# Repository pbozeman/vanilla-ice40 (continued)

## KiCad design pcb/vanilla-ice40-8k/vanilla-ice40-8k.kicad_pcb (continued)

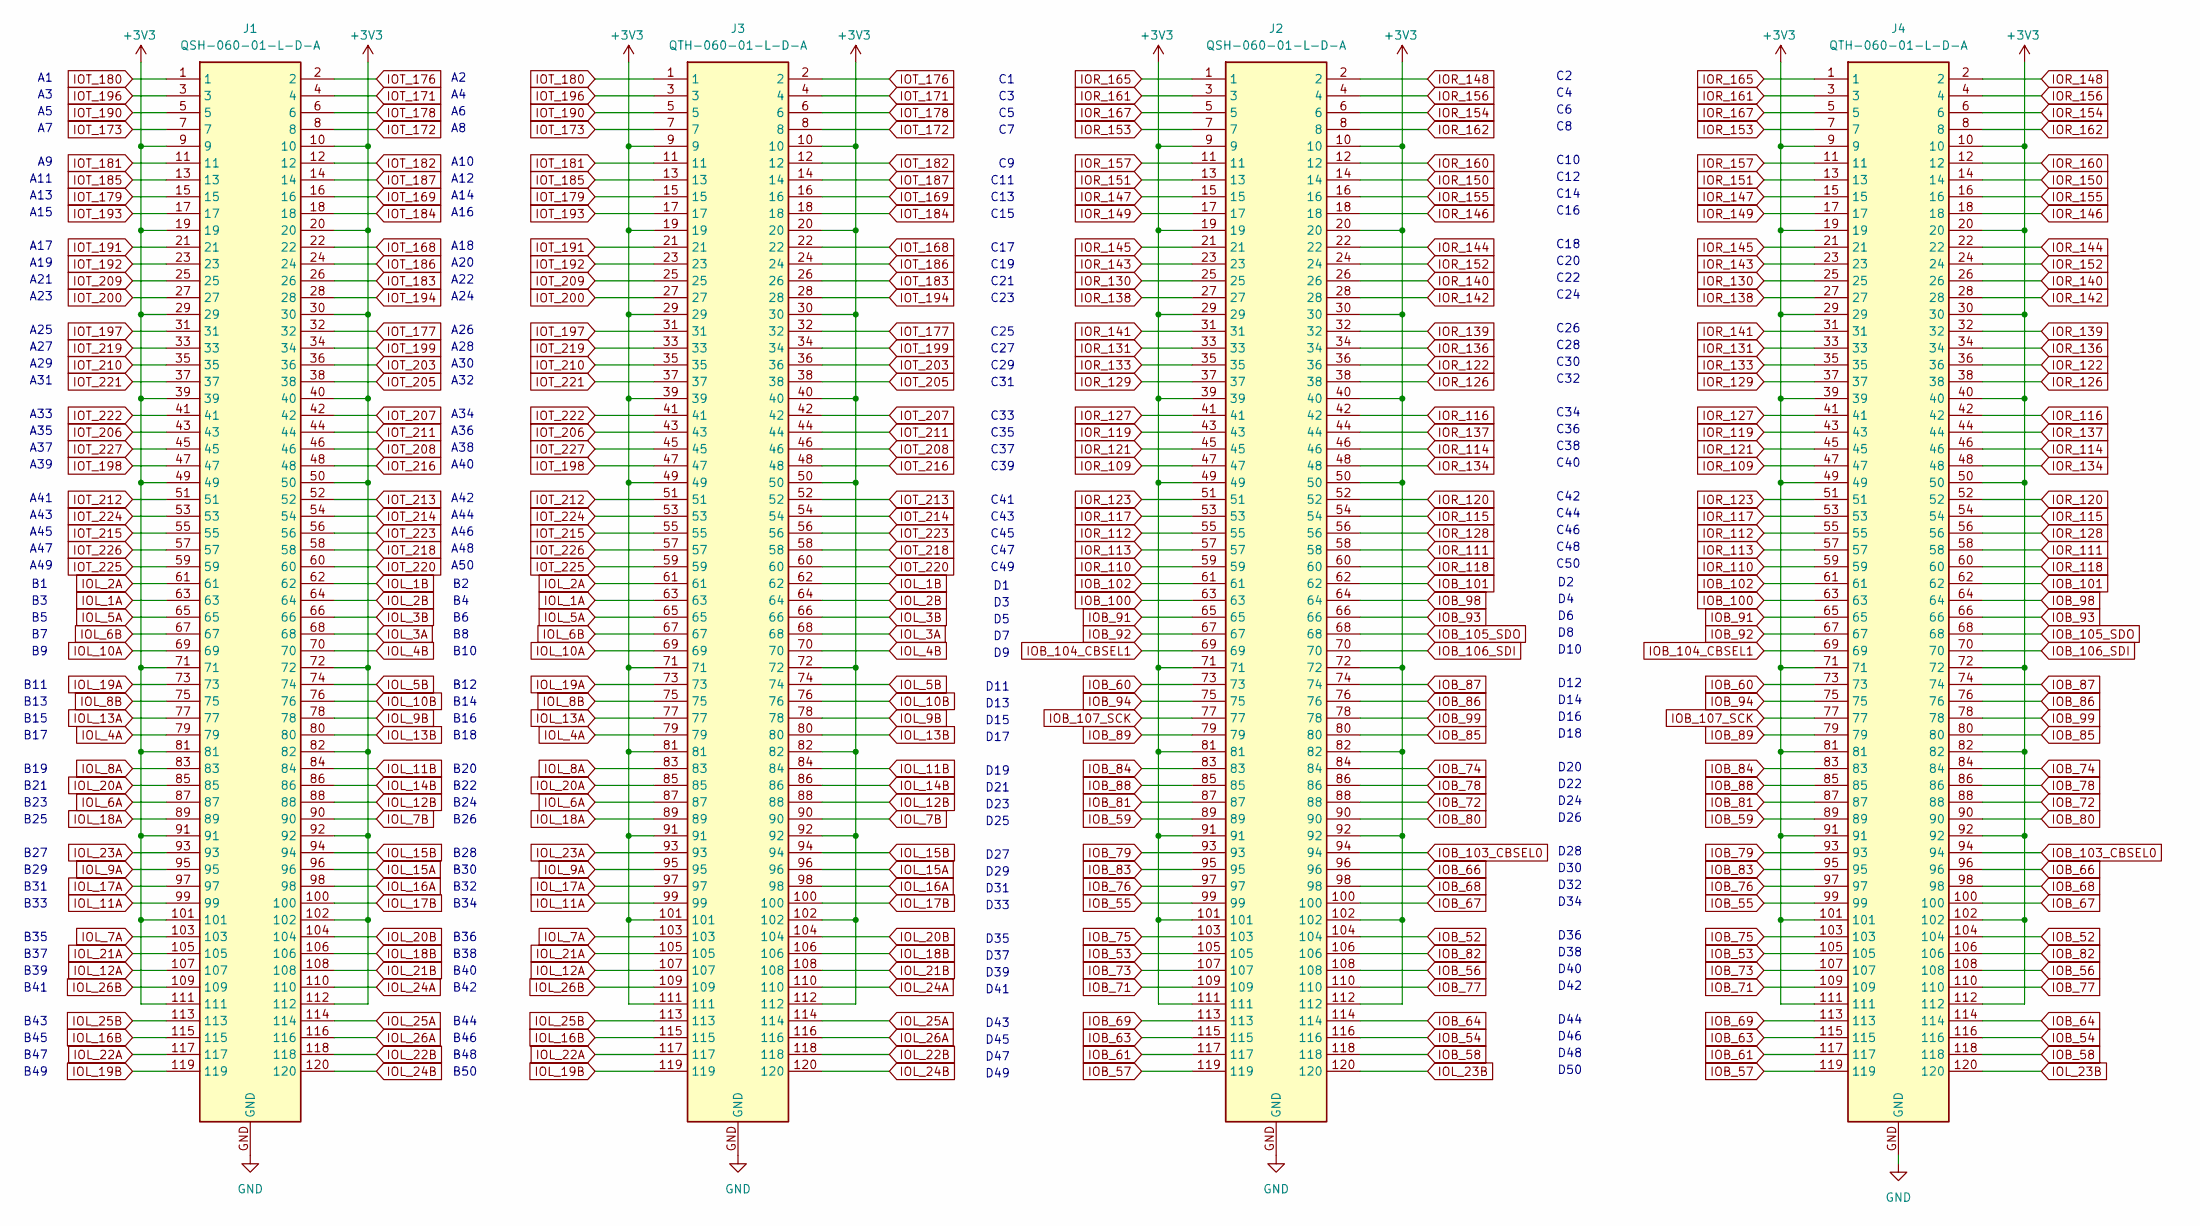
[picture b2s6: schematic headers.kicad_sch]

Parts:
J1, J2: QSH-060-01-L-D-A; SAMTEC_QSH-060-01-X-D-A
J3, J4: QTH-060-01-L-D-A; SAMTEC_QTH-060-01-X-D-A

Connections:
+3V3: J1.9, J1.10, J1.19, J1.20, J1.29, J1.30, J1.39, J1.40, J1.49, J1.50, J1.71, J1.72, J1.81, J1.82, J1.91, J1.92, J1.101, J1.102, J1.111, J1.112, J2.9, J2.10, J2.19, J2.20, J2.29, J2.30, J2.39, J2.40, J2.49, J2.50, J2.71, J2.72, J2.81, J2.82, J2.91, J2.92, J2.101, J2.102, J2.111, J2.112, J3.9, J3.10, J3.19, J3.20, J3.29, J3.30, J3.39, J3.40, J3.49, J3.50, J3.71, J3.72, J3.81, J3.82, J3.91, J3.92, J3.101, J3.102, J3.111, J3.112, J4.9, J4.10, J4.19, J4.20, J4.29, J4.30, J4.39, J4.40, J4.49, J4.50, J4.71, J4.72, J4.81, J4.82, J4.91, J4.92, J4.101, J4.102, J4.111, J4.112; also elsewhere on the board
GND: J1.GND, J2.GND, J3.GND, J4.GND; also elsewhere on the board
IOB_52: J2.104, J4.104; also elsewhere on the board
IOB_53: J2.105, J4.105; also elsewhere on the board
IOB_54: J2.116, J4.116; also elsewhere on the board
IOB_55: J2.99, J4.99; also elsewhere on the board
IOB_56: J2.108, J4.108; also elsewhere on the board
IOB_57: J2.119, J4.119; also elsewhere on the board
IOB_58: J2.118, J4.118; also elsewhere on the board
IOB_59: J2.89, J4.89; also elsewhere on the board
IOB_60: J2.73, J4.73; also elsewhere on the board
IOB_61: J2.117, J4.117; also elsewhere on the board
IOB_63: J2.115, J4.115; also elsewhere on the board
IOB_64: J2.114, J4.114; also elsewhere on the board
IOB_66: J2.96, J4.96; also elsewhere on the board
IOB_67: J2.100, J4.100; also elsewhere on the board
IOB_68: J2.98, J4.98; also elsewhere on the board
IOB_69: J2.113, J4.113; also elsewhere on the board
IOB_71: J2.109, J4.109; also elsewhere on the board
IOB_72: J2.88, J4.88; also elsewhere on the board
IOB_73: J2.107, J4.107; also elsewhere on the board
IOB_74: J2.84, J4.84; also elsewhere on the board
IOB_75: J2.103, J4.103; also elsewhere on the board
IOB_76: J2.97, J4.97; also elsewhere on the board
IOB_77: J2.110, J4.110; also elsewhere on the board
IOB_78: J2.86, J4.86; also elsewhere on the board
IOB_79: J2.93, J4.93; also elsewhere on the board
IOB_80: J2.90, J4.90; also elsewhere on the board
IOB_81: J2.87, J4.87; also elsewhere on the board
IOB_82: J2.106, J4.106; also elsewhere on the board
IOB_83: J2.95, J4.95; also elsewhere on the board
IOB_84: J2.83, J4.83; also elsewhere on the board
IOB_85: J2.80, J4.80; also elsewhere on the board
IOB_86: J2.76, J4.76; also elsewhere on the board
IOB_87: J2.74, J4.74; also elsewhere on the board
IOB_88: J2.85, J4.85; also elsewhere on the board
IOB_89: J2.79, J4.79; also elsewhere on the board
IOB_91: J2.65, J4.65; also elsewhere on the board
IOB_92: J2.67, J4.67; also elsewhere on the board
IOB_93: J2.66, J4.66; also elsewhere on the board
IOB_94: J2.75, J4.75; also elsewhere on the board
IOB_98: J2.64, J4.64; also elsewhere on the board
IOB_99: J2.78, J4.78; also elsewhere on the board
IOB_100: J2.63, J4.63; also elsewhere on the board
IOB_101: J2.62, J4.62; also elsewhere on the board
IOB_102: J2.61, J4.61; also elsewhere on the board
IOB_103_CBSEL0: J2.94, J4.94; also elsewhere on the board
IOB_104_CBSEL1: J2.69, J4.69; also elsewhere on the board
IOB_105_SDO: J2.68, J4.68; also elsewhere on the board
IOB_106_SDI: J2.70, J4.70; also elsewhere on the board
IOB_107_SCK: J2.77, J4.77; also elsewhere on the board
IOL_1A: J1.63, J3.63; also elsewhere on the board
IOL_1B: J1.62, J3.62; also elsewhere on the board
IOL_2A: J1.61, J3.61; also elsewhere on the board
IOL_2B: J1.64, J3.64; also elsewhere on the board
IOL_3A: J1.68, J3.68; also elsewhere on the board
IOL_3B: J1.66, J3.66; also elsewhere on the board
IOL_4A: J1.79, J3.79; also elsewhere on the board
IOL_4B: J1.70, J3.70; also elsewhere on the board
IOL_5A: J1.65, J3.65; also elsewhere on the board
IOL_5B: J1.74, J3.74; also elsewhere on the board
IOL_6A: J1.87, J3.87; also elsewhere on the board
IOL_6B: J1.67, J3.67; also elsewhere on the board
IOL_7A: J1.103, J3.103; also elsewhere on the board
IOL_7B: J1.90, J3.90; also elsewhere on the board
IOL_8A: J1.83, J3.83; also elsewhere on the board
IOL_8B: J1.75, J3.75; also elsewhere on the board
IOL_9A: J1.95, J3.95; also elsewhere on the board
IOL_9B: J1.78, J3.78; also elsewhere on the board
IOL_10A: J1.69, J3.69; also elsewhere on the board
IOL_10B: J1.76, J3.76; also elsewhere on the board
IOL_11A: J1.99, J3.99; also elsewhere on the board
IOL_11B: J1.84, J3.84; also elsewhere on the board
IOL_12A: J1.107, J3.107; also elsewhere on the board
IOL_12B: J1.88, J3.88; also elsewhere on the board
IOL_13A: J1.77, J3.77; also elsewhere on the board
IOL_13B: J1.80, J3.80; also elsewhere on the board
IOL_14B: J1.86, J3.86; also elsewhere on the board
IOL_15A: J1.96, J3.96; also elsewhere on the board
IOL_15B: J1.94, J3.94; also elsewhere on the board
IOL_16A: J1.98, J3.98; also elsewhere on the board
IOL_16B: J1.115, J3.115; also elsewhere on the board
IOL_17A: J1.97, J3.97; also elsewhere on the board
IOL_17B: J1.100, J3.100; also elsewhere on the board
IOL_18A: J1.89, J3.89; also elsewhere on the board
IOL_18B: J1.106, J3.106; also elsewhere on the board
IOL_19A: J1.73, J3.73; also elsewhere on the board
IOL_19B: J1.119, J3.119; also elsewhere on the board
IOL_20A: J1.85, J3.85; also elsewhere on the board
IOL_20B: J1.104, J3.104; also elsewhere on the board
IOL_21A: J1.105, J3.105; also elsewhere on the board
IOL_21B: J1.108, J3.108; also elsewhere on the board
IOL_22A: J1.117, J3.117; also elsewhere on the board
IOL_22B: J1.118, J3.118; also elsewhere on the board
IOL_23A: J1.93, J3.93; also elsewhere on the board
IOL_23B: J2.120, J4.120; also elsewhere on the board
IOL_24A: J1.110, J3.110; also elsewhere on the board
IOL_24B: J1.120, J3.120; also elsewhere on the board
IOL_25A: J1.114, J3.114; also elsewhere on the board
IOL_25B: J1.113, J3.113; also elsewhere on the board
IOL_26A: J1.116, J3.116; also elsewhere on the board
IOL_26B: J1.109, J3.109; also elsewhere on the board
IOR_109: J2.47, J4.47; also elsewhere on the board
IOR_110: J2.59, J4.59; also elsewhere on the board
IOR_111: J2.58, J4.58; also elsewhere on the board
IOR_112: J2.55, J4.55; also elsewhere on the board
IOR_113: J2.57, J4.57; also elsewhere on the board
IOR_114: J2.46, J4.46; also elsewhere on the board
IOR_115: J2.54, J4.54; also elsewhere on the board
IOR_116: J2.42, J4.42; also elsewhere on the board
IOR_117: J2.53, J4.53; also elsewhere on the board
IOR_118: J2.60, J4.60; also elsewhere on the board
IOR_119: J2.43, J4.43; also elsewhere on the board
IOR_120: J2.52, J4.52; also elsewhere on the board
IOR_121: J2.45, J4.45; also elsewhere on the board
IOR_122: J2.36, J4.36; also elsewhere on the board
IOR_123: J2.51, J4.51; also elsewhere on the board
IOR_126: J2.38, J4.38; also elsewhere on the board
IOR_127: J2.41, J4.41; also elsewhere on the board
IOR_128: J2.56, J4.56; also elsewhere on the board
IOR_129: J2.37, J4.37; also elsewhere on the board
IOR_130: J2.25, J4.25; also elsewhere on the board
IOR_131: J2.33, J4.33; also elsewhere on the board
IOR_133: J2.35, J4.35; also elsewhere on the board
IOR_134: J2.48, J4.48; also elsewhere on the board
IOR_136: J2.34, J4.34; also elsewhere on the board
IOR_137: J2.44, J4.44; also elsewhere on the board
IOR_138: J2.27, J4.27; also elsewhere on the board
IOR_139: J2.32, J4.32; also elsewhere on the board
IOR_140: J2.26, J4.26; also elsewhere on the board
IOR_141: J2.31, J4.31; also elsewhere on the board
IOR_142: J2.28, J4.28; also elsewhere on the board
IOR_143: J2.23, J4.23; also elsewhere on the board
IOR_144: J2.22, J4.22; also elsewhere on the board
IOR_145: J2.21, J4.21; also elsewhere on the board
IOR_146: J2.18, J4.18; also elsewhere on the board
IOR_147: J2.15, J4.15; also elsewhere on the board
IOR_148: J2.2, J4.2; also elsewhere on the board
IOR_149: J2.17, J4.17; also elsewhere on the board
IOR_150: J2.14, J4.14; also elsewhere on the board
IOR_151: J2.13, J4.13; also elsewhere on the board
IOR_152: J2.24, J4.24; also elsewhere on the board
IOR_153: J2.7, J4.7; also elsewhere on the board
IOR_154: J2.6, J4.6; also elsewhere on the board
IOR_155: J2.16, J4.16; also elsewhere on the board
IOR_156: J2.4, J4.4; also elsewhere on the board
IOR_157: J2.11, J4.11; also elsewhere on the board
IOR_160: J2.12, J4.12; also elsewhere on the board
IOR_161: J2.3, J4.3; also elsewhere on the board
IOR_162: J2.8, J4.8; also elsewhere on the board
IOR_165: J2.1, J4.1; also elsewhere on the board
IOR_167: J2.5, J4.5; also elsewhere on the board
IOT_168: J1.22, J3.22; also elsewhere on the board
IOT_169: J1.16, J3.16; also elsewhere on the board
IOT_171: J1.4, J3.4; also elsewhere on the board
IOT_172: J1.8, J3.8; also elsewhere on the board
IOT_173: J1.7, J3.7; also elsewhere on the board
IOT_176: J1.2, J3.2; also elsewhere on the board
IOT_177: J1.32, J3.32; also elsewhere on the board
IOT_178: J1.6, J3.6; also elsewhere on the board
IOT_179: J1.15, J3.15; also elsewhere on the board
IOT_180: J1.1, J3.1; also elsewhere on the board
IOT_181: J1.11, J3.11; also elsewhere on the board
IOT_182: J1.12, J3.12; also elsewhere on the board
IOT_183: J1.26, J3.26; also elsewhere on the board
IOT_184: J1.18, J3.18; also elsewhere on the board
IOT_185: J1.13, J3.13; also elsewhere on the board
IOT_186: J1.24, J3.24; also elsewhere on the board
IOT_187: J1.14, J3.14; also elsewhere on the board
IOT_190: J1.5, J3.5; also elsewhere on the board
IOT_191: J1.21, J3.21; also elsewhere on the board
IOT_192: J1.23, J3.23; also elsewhere on the board
IOT_193: J1.17, J3.17; also elsewhere on the board
IOT_194: J1.28, J3.28; also elsewhere on the board
IOT_196: J1.3, J3.3; also elsewhere on the board
IOT_197: J1.31, J3.31; also elsewhere on the board
IOT_198: J1.47, J3.47; also elsewhere on the board
IOT_199: J1.34, J3.34; also elsewhere on the board
IOT_200: J1.27, J3.27; also elsewhere on the board
IOT_203: J1.36, J3.36; also elsewhere on the board
IOT_205: J1.38, J3.38; also elsewhere on the board
IOT_206: J1.43, J3.43; also elsewhere on the board
IOT_207: J1.42, J3.42; also elsewhere on the board
IOT_208: J1.46, J3.46; also elsewhere on the board
IOT_209: J1.25, J3.25; also elsewhere on the board
IOT_210: J1.35, J3.35; also elsewhere on the board
IOT_211: J1.44, J3.44; also elsewhere on the board
IOT_212: J1.51, J3.51; also elsewhere on the board
IOT_213: J1.52, J3.52; also elsewhere on the board
IOT_214: J1.54, J3.54; also elsewhere on the board
IOT_215: J1.55, J3.55; also elsewhere on the board
IOT_216: J1.48, J3.48; also elsewhere on the board
IOT_218: J1.58, J3.58; also elsewhere on the board
IOT_219: J1.33, J3.33; also elsewhere on the board
IOT_220: J1.60, J3.60; also elsewhere on the board
IOT_221: J1.37, J3.37; also elsewhere on the board
IOT_222: J1.41, J3.41; also elsewhere on the board
IOT_223: J1.56, J3.56; also elsewhere on the board
IOT_224: J1.53, J3.53; also elsewhere on the board
IOT_225: J1.59, J3.59; also elsewhere on the board
IOT_226: J1.57, J3.57; also elsewhere on the board
IOT_227: J1.45, J3.45; also elsewhere on the board

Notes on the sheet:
C41
C23
C16
B42
B10
C43
B33
B31
B15
C30
D17
A38
D41
B24
B25
C50
D42
C14
C33
B13
D19
C18
A22
D18
A37
A28
A17
A33
D25
B21
D15
B23
B22
D21
A35
A42
D12
C48
C25
D31

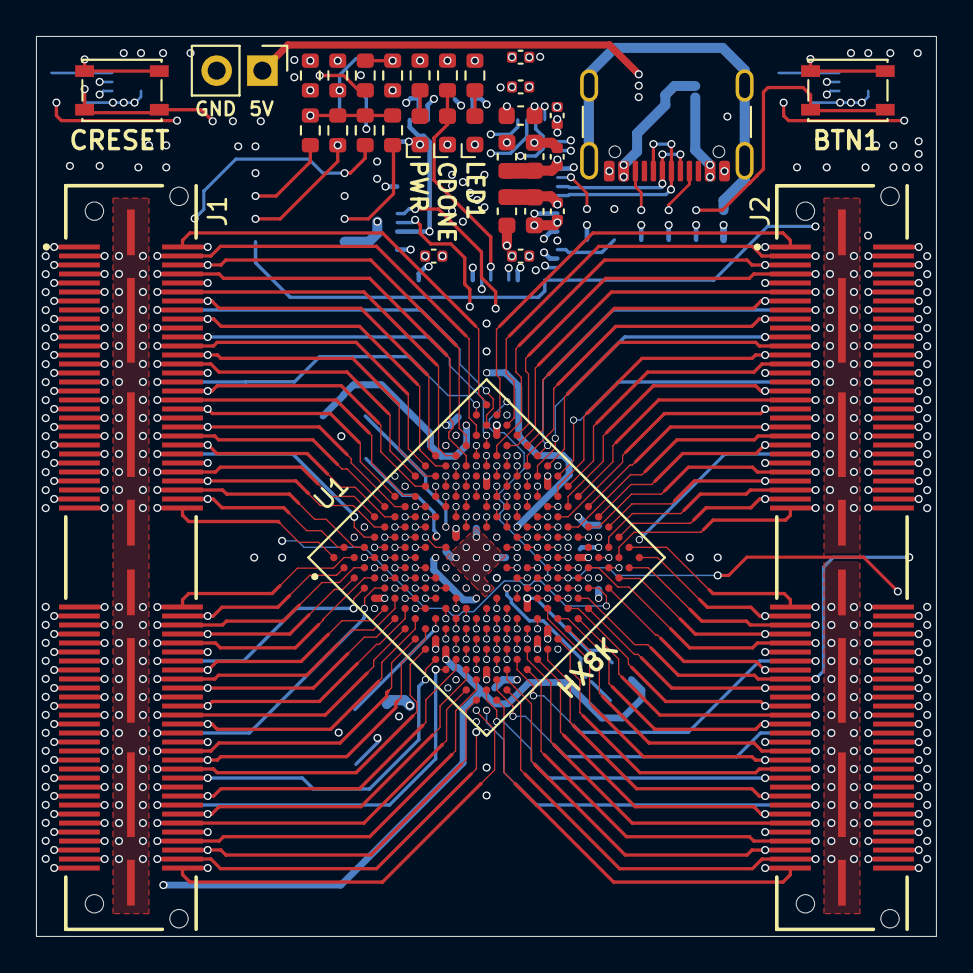
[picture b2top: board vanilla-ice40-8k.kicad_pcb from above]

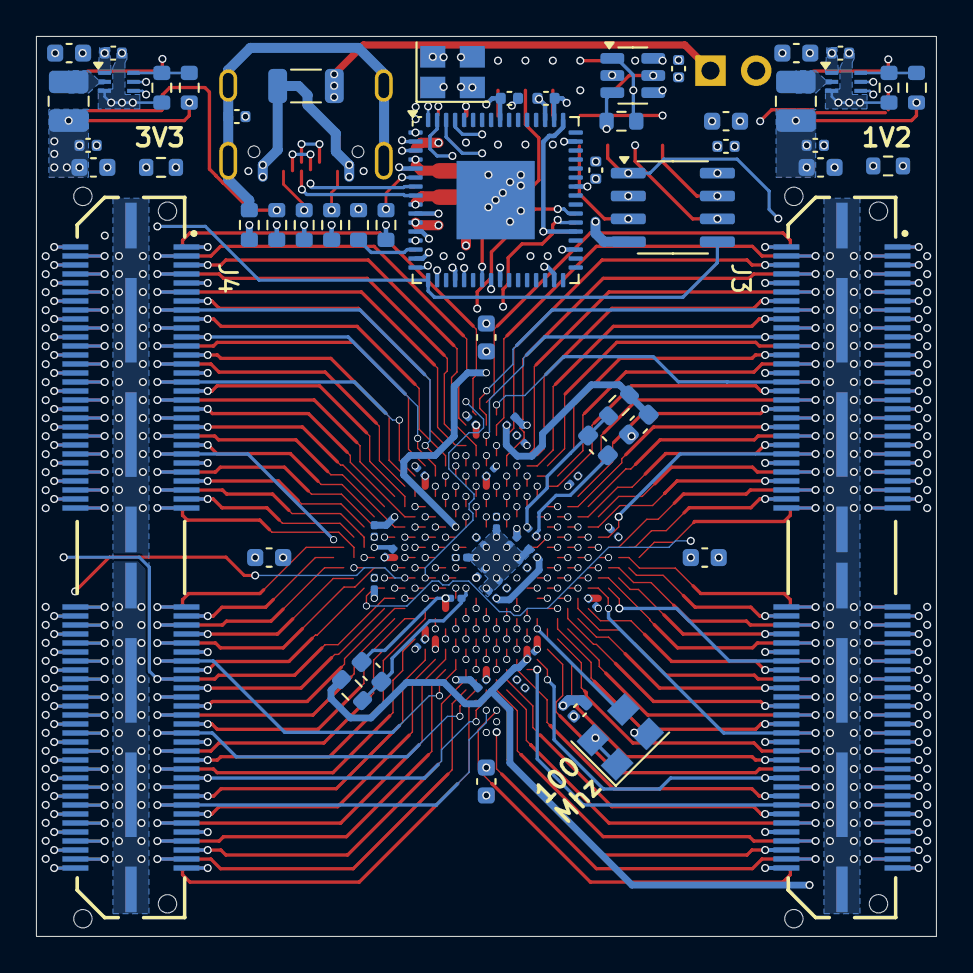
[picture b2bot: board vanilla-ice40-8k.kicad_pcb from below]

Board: 8 copper layers, 50.0 x 50.0 mm, 109 parts (76 on the bottom side), 243 nets.

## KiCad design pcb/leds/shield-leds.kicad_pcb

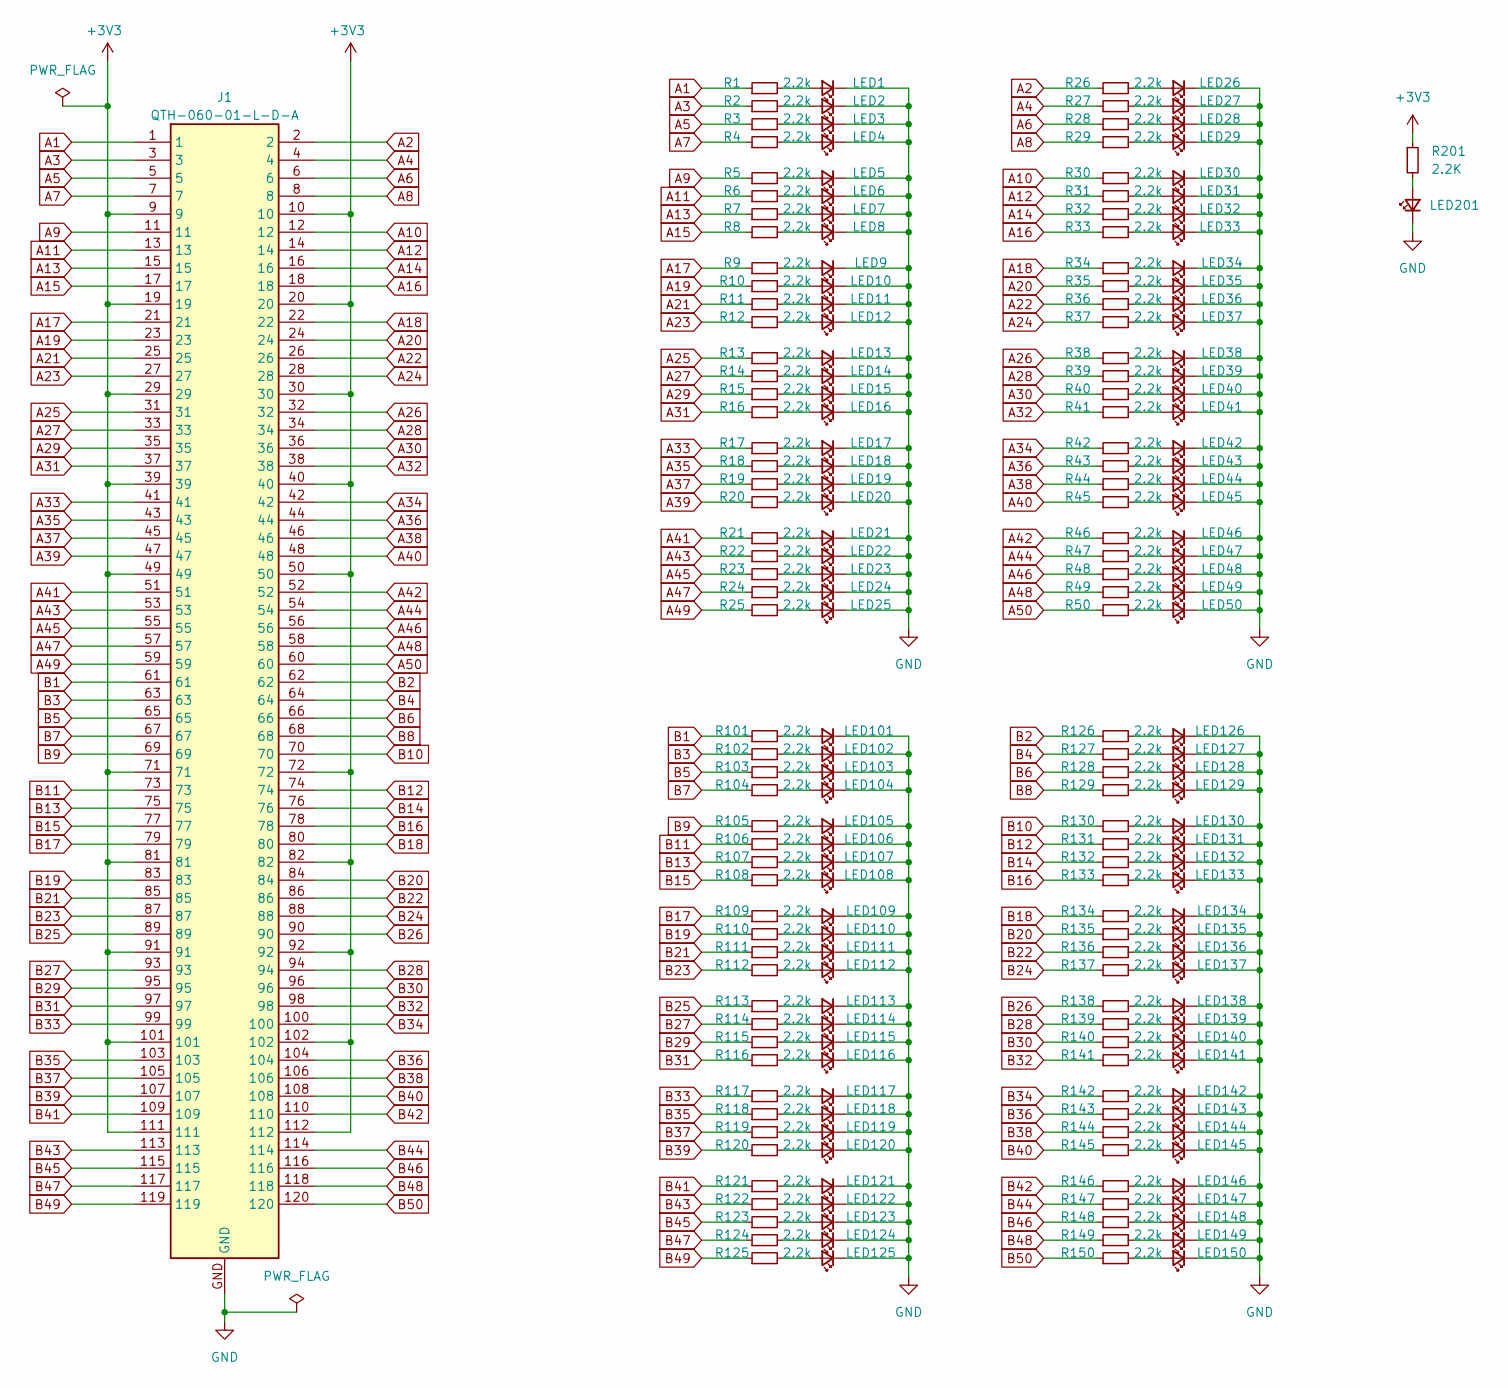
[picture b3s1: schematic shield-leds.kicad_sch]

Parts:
J1: QTH-060-01-L-D-A; SAMTEC_QTH-060-01-X-D-A
LED1, LED2, LED3, LED4, LED5, LED6, LED7, LED8, LED9, LED10, LED11, LED12, LED13, LED14, LED15, LED16, LED17, LED18, LED19, LED20, LED21, LED22, LED23, LED24, LED25, LED26, LED27, LED28, LED29, LED30, LED31, LED32, LED33, LED34, LED35, LED36, LED37, LED38, LED39, LED40, LED41, LED42, LED43, LED44, LED45, LED46, LED47, LED48, LED49, LED50, LED101, LED102, LED103, LED104, LED105, LED106, LED107, LED108, LED109, LED110, LED111, LED112, LED113, LED114, LED115, LED116, LED117, LED118, LED119, LED120, LED121, LED122, LED123, LED124, LED125, LED126, LED127, LED128, LED129, LED130, LED131, LED132, LED133, LED134, LED135, LED136, LED137, LED138, LED139, LED140, LED141, LED142, LED143, LED144, LED145, LED146, LED147, LED148, LED149, LED150: Blue; D_0603_1608Metric; LCSC Part # C434421
LED201: BLU; D_0603_1608Metric; LCSC Part # C434421
R1, R2, R3, R4, R5, R6, R7, R8, R9, R10, R11, R12, R13, R14, R15, R16, R17, R18, R19, R20, R21, R22, R23, R24, R25, R26, R27, R28, R29, R30, R31, R32, R33, R34, R35, R36, R37, R38, R39, R40, R41, R42, R43, R44, R45, R46, R47, R48, R49, R50, R101, R102, R103, R104, R105, R106, R107, R108, R109, R110, R111, R112, R113, R114, R115, R116, R117, R118, R119, R120, R121, R122, R123, R124, R125, R126, R127, R128, R129, R130, R131, R132, R133, R134, R135, R136, R137, R138, R139, R140, R141, R142, R143, R144, R145, R146, R147, R148, R149, R150: 2.2k; R_0603_1608Metric; LCSC Part # C4190
R201: 2.2K; R_0603_1608Metric; LCSC Part # C4190

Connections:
+3V3: J1.9, J1.10, J1.19, J1.20, J1.29, J1.30, J1.39, J1.40, J1.49, J1.50, J1.71, J1.72, J1.81, J1.82, J1.91, J1.92, J1.101, J1.102, J1.111, J1.112, R201.1
A1: J1.1, R1.1
A2: J1.2, R26.1
A3: J1.3, R2.1
A4: J1.4, R27.1
A5: J1.5, R3.1
A6: J1.6, R28.1
A7: J1.7, R4.1
A8: J1.8, R29.1
A9: J1.11, R5.1
A10: J1.12, R30.1
A11: J1.13, R6.1
A12: J1.14, R31.1
A13: J1.15, R7.1
A14: J1.16, R32.1
A15: J1.17, R8.1
A16: J1.18, R33.1
A17: J1.21, R9.1
A18: J1.22, R34.1
A19: J1.23, R10.1
A20: J1.24, R35.1
A21: J1.25, R11.1
A22: J1.26, R36.1
A23: J1.27, R12.1
A24: J1.28, R37.1
A25: J1.31, R13.1
A26: J1.32, R38.1
A27: J1.33, R14.1
A28: J1.34, R39.1
A29: J1.35, R15.1
A30: J1.36, R40.1
A31: J1.37, R16.1
A32: J1.38, R41.1
A33: J1.41, R17.1
A34: J1.42, R42.1
A35: J1.43, R18.1
A36: J1.44, R43.1
A37: J1.45, R19.1
A38: J1.46, R44.1
A39: J1.47, R20.1
A40: J1.48, R45.1
A41: J1.51, R21.1
A42: J1.52, R46.1
A43: J1.53, R22.1
A44: J1.54, R47.1
A45: J1.55, R23.1
A46: J1.56, R48.1
A47: J1.57, R24.1
A48: J1.58, R49.1
A49: J1.59, R25.1
A50: J1.60, R50.1
B1: J1.61, R101.1
B2: J1.62, R126.1
B3: J1.63, R102.1
B4: J1.64, R127.1
B5: J1.65, R103.1
B6: J1.66, R128.1
B7: J1.67, R104.1
B8: J1.68, R129.1
B9: J1.69, R105.1
B10: J1.70, R130.1
B11: J1.73, R106.1
B12: J1.74, R131.1
B13: J1.75, R107.1
B14: J1.76, R132.1
B15: J1.77, R108.1
B16: J1.78, R133.1
B17: J1.79, R109.1
B18: J1.80, R134.1
B19: J1.83, R110.1
B20: J1.84, R135.1
B21: J1.85, R111.1
B22: J1.86, R136.1
B23: J1.87, R112.1
B24: J1.88, R137.1
B25: J1.89, R113.1
B26: J1.90, R138.1
B27: J1.93, R114.1
B28: J1.94, R139.1
B29: J1.95, R115.1
B30: J1.96, R140.1
B31: J1.97, R116.1
B32: J1.98, R141.1
B33: J1.99, R117.1
B34: J1.100, R142.1
B35: J1.103, R118.1
B36: J1.104, R143.1
B37: J1.105, R119.1
B38: J1.106, R144.1
B39: J1.107, R120.1
B40: J1.108, R145.1
B41: J1.109, R121.1
B42: J1.110, R146.1
B43: J1.113, R122.1
B44: J1.114, R147.1
B45: J1.115, R123.1
B46: J1.116, R148.1
B47: J1.117, R124.1
B48: J1.118, R149.1
B49: J1.119, R125.1
B50: J1.120, R150.1
GND: J1.GND, LED1.1 (K), LED2.1 (K), LED3.1 (K), LED4.1 (K), LED5.1 (K), LED6.1 (K), LED7.1 (K), LED8.1 (K), LED9.1 (K), LED10.1 (K), LED11.1 (K), LED12.1 (K), LED13.1 (K), LED14.1 (K), LED15.1 (K), LED16.1 (K), LED17.1 (K), LED18.1 (K), LED19.1 (K), LED20.1 (K), LED21.1 (K), LED22.1 (K), LED23.1 (K), LED24.1 (K), LED25.1 (K), LED26.1 (K), LED27.1 (K), LED28.1 (K), LED29.1 (K), LED30.1 (K), LED31.1 (K), LED32.1 (K), LED33.1 (K), LED34.1 (K), LED35.1 (K), LED36.1 (K), LED37.1 (K), LED38.1 (K), LED39.1 (K), LED40.1 (K), LED41.1 (K), LED42.1 (K), LED43.1 (K), LED44.1 (K), LED45.1 (K), LED46.1 (K), LED47.1 (K), LED48.1 (K), LED49.1 (K), LED50.1 (K), LED101.1 (K), LED102.1 (K), LED103.1 (K), LED104.1 (K), LED105.1 (K), LED106.1 (K), LED107.1 (K), LED108.1 (K), LED109.1 (K), LED110.1 (K), LED111.1 (K), LED112.1 (K), LED113.1 (K), LED114.1 (K), LED115.1 (K), LED116.1 (K), LED117.1 (K), LED118.1 (K), LED119.1 (K), LED120.1 (K), LED121.1 (K), LED122.1 (K), LED123.1 (K), LED124.1 (K), LED125.1 (K), LED126.1 (K), LED127.1 (K), LED128.1 (K), LED129.1 (K), LED130.1 (K), LED131.1 (K), LED132.1 (K), LED133.1 (K), LED134.1 (K), LED135.1 (K), LED136.1 (K), LED137.1 (K), LED138.1 (K), LED139.1 (K), LED140.1 (K), LED141.1 (K), LED142.1 (K), LED143.1 (K), LED144.1 (K), LED145.1 (K), LED146.1 (K), LED147.1 (K), LED148.1 (K), LED149.1 (K), LED150.1 (K), LED201.1 (K)
unnamed: LED1.2 (A), R1.2
unnamed: LED2.2 (A), R2.2
unnamed: LED3.2 (A), R3.2
unnamed: LED4.2 (A), R4.2
unnamed: LED5.2 (A), R5.2
unnamed: LED6.2 (A), R6.2
unnamed: LED7.2 (A), R7.2
unnamed: LED8.2 (A), R8.2
unnamed: LED9.2 (A), R9.2
unnamed: LED10.2 (A), R10.2
unnamed: LED11.2 (A), R11.2
unnamed: LED12.2 (A), R12.2
unnamed: LED13.2 (A), R13.2
unnamed: LED14.2 (A), R14.2
unnamed: LED15.2 (A), R15.2
unnamed: LED16.2 (A), R16.2
unnamed: LED17.2 (A), R17.2
unnamed: LED18.2 (A), R18.2
unnamed: LED19.2 (A), R19.2
unnamed: LED20.2 (A), R20.2
unnamed: LED21.2 (A), R21.2
unnamed: LED22.2 (A), R22.2
unnamed: LED23.2 (A), R23.2
unnamed: LED24.2 (A), R24.2
unnamed: LED25.2 (A), R25.2
unnamed: LED26.2 (A), R26.2
unnamed: LED27.2 (A), R27.2
unnamed: LED28.2 (A), R28.2
unnamed: LED29.2 (A), R29.2
unnamed: LED30.2 (A), R30.2
unnamed: LED31.2 (A), R31.2
unnamed: LED32.2 (A), R32.2
unnamed: LED33.2 (A), R33.2
unnamed: LED34.2 (A), R34.2
unnamed: LED35.2 (A), R35.2
unnamed: LED36.2 (A), R36.2
unnamed: LED37.2 (A), R37.2
unnamed: LED38.2 (A), R38.2
unnamed: LED39.2 (A), R39.2
unnamed: LED40.2 (A), R40.2
unnamed: LED41.2 (A), R41.2
unnamed: LED42.2 (A), R42.2
unnamed: LED43.2 (A), R43.2
unnamed: LED44.2 (A), R44.2
unnamed: LED45.2 (A), R45.2
unnamed: LED46.2 (A), R46.2
unnamed: LED47.2 (A), R47.2
unnamed: LED48.2 (A), R48.2
unnamed: LED49.2 (A), R49.2
unnamed: LED50.2 (A), R50.2
unnamed: LED101.2 (A), R101.2
unnamed: LED102.2 (A), R102.2
unnamed: LED103.2 (A), R103.2
unnamed: LED104.2 (A), R104.2
unnamed: LED105.2 (A), R105.2
unnamed: LED106.2 (A), R106.2
unnamed: LED107.2 (A), R107.2
unnamed: LED108.2 (A), R108.2
unnamed: LED109.2 (A), R109.2
unnamed: LED110.2 (A), R110.2
unnamed: LED111.2 (A), R111.2
unnamed: LED112.2 (A), R112.2
unnamed: LED113.2 (A), R113.2
unnamed: LED114.2 (A), R114.2
unnamed: LED115.2 (A), R115.2
unnamed: LED116.2 (A), R116.2
unnamed: LED117.2 (A), R117.2
unnamed: LED118.2 (A), R118.2
unnamed: LED119.2 (A), R119.2
unnamed: LED120.2 (A), R120.2
unnamed: LED121.2 (A), R121.2
unnamed: LED122.2 (A), R122.2
unnamed: LED123.2 (A), R123.2
unnamed: LED124.2 (A), R124.2
unnamed: LED125.2 (A), R125.2
unnamed: LED126.2 (A), R126.2
unnamed: LED127.2 (A), R127.2
unnamed: LED128.2 (A), R128.2
unnamed: LED129.2 (A), R129.2
unnamed: LED130.2 (A), R130.2
unnamed: LED131.2 (A), R131.2
unnamed: LED132.2 (A), R132.2
unnamed: LED133.2 (A), R133.2
unnamed: LED134.2 (A), R134.2
unnamed: LED135.2 (A), R135.2
unnamed: LED136.2 (A), R136.2
unnamed: LED137.2 (A), R137.2
unnamed: LED138.2 (A), R138.2
unnamed: LED139.2 (A), R139.2
unnamed: LED140.2 (A), R140.2
unnamed: LED141.2 (A), R141.2
unnamed: LED142.2 (A), R142.2
unnamed: LED143.2 (A), R143.2
unnamed: LED144.2 (A), R144.2
unnamed: LED145.2 (A), R145.2
unnamed: LED146.2 (A), R146.2
unnamed: LED147.2 (A), R147.2
unnamed: LED148.2 (A), R148.2
unnamed: LED149.2 (A), R149.2
unnamed: LED150.2 (A), R150.2
unnamed: LED201.2 (A), R201.2

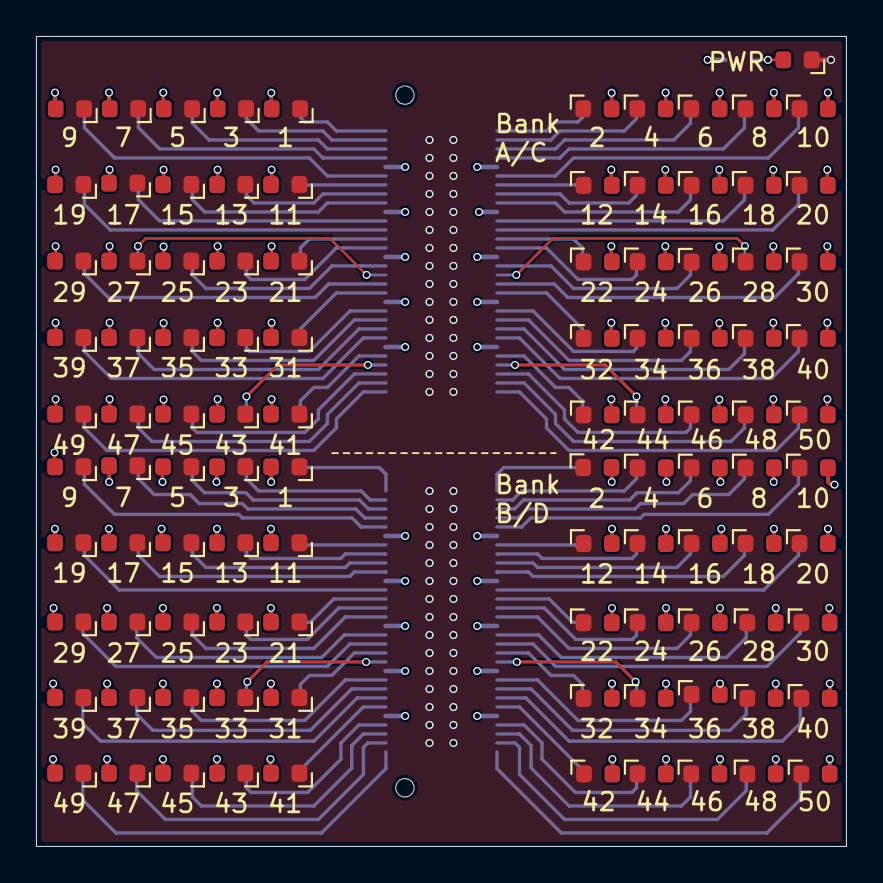
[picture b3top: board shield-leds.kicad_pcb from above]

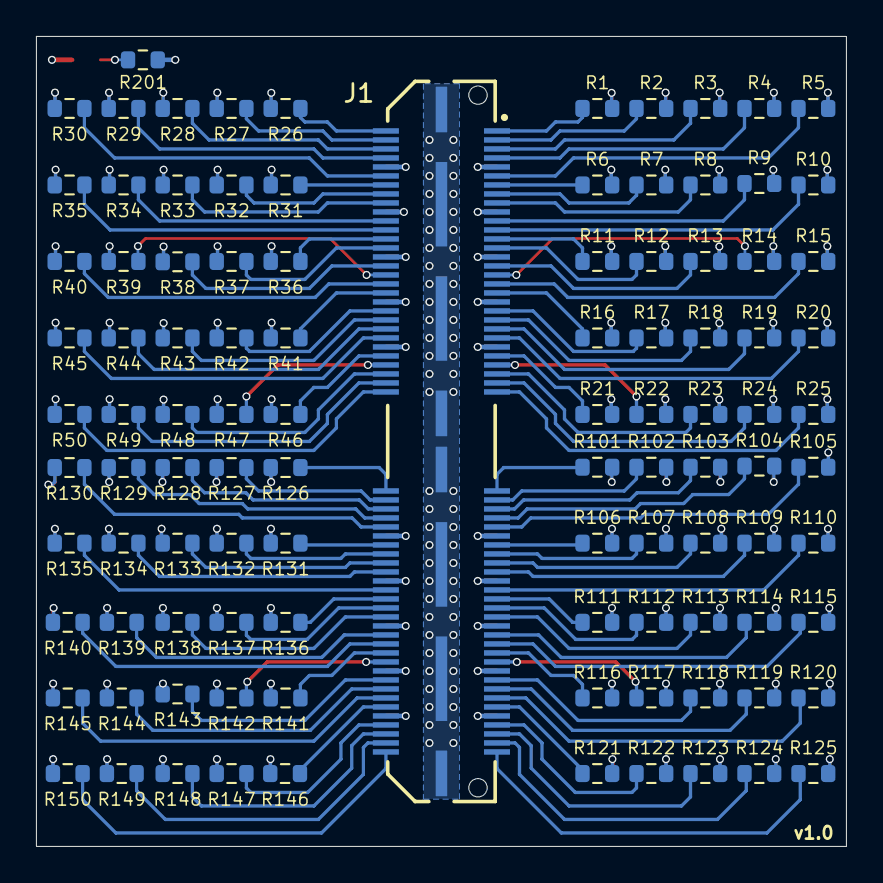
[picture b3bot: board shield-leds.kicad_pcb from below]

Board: 4 copper layers, 45.0 x 45.0 mm, 203 parts (102 on the bottom side), 203 nets.
